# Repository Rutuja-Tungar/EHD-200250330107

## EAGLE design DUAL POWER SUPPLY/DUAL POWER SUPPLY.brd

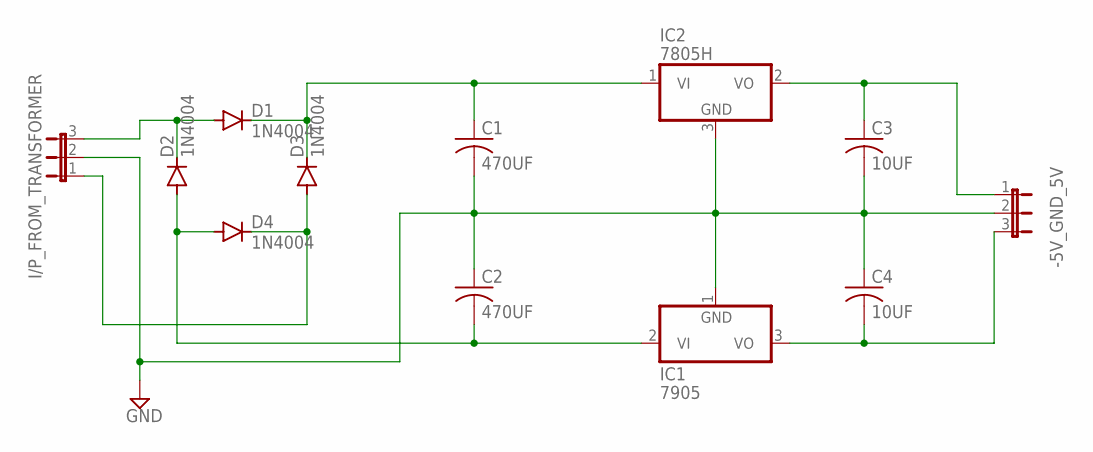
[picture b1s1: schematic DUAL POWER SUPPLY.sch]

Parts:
-5V_GND_5V: JP2W
C1, C2: 470UF; C025-024X044
C3, C4: 10UF; C025-024X044
D1, D2, D3, D4: 1N4004; DO41-10
I/P_FROM_TRANSFORMER: JP2W
IC1: 7905; TO39
IC2: 7805H; TO39

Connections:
GND: -5V_GND_5V.2, C1.2, C2.1, C3.2, C4.1, I/P_FROM_TRANSFORMER.2, IC1.1 (GND), IC2.3 (GND)
unnamed: D1.A, D2.C, I/P_FROM_TRANSFORMER.3
unnamed: C2.2, D2.A, D4.A, IC1.2 (VI)
unnamed: D3.A, D4.C, I/P_FROM_TRANSFORMER.1
unnamed: C1.1, D1.C, D3.C, IC2.1 (VI)
unnamed: -5V_GND_5V.1, C3.1, IC2.2 (VO)
unnamed: -5V_GND_5V.3, C4.2, IC1.3 (VO)

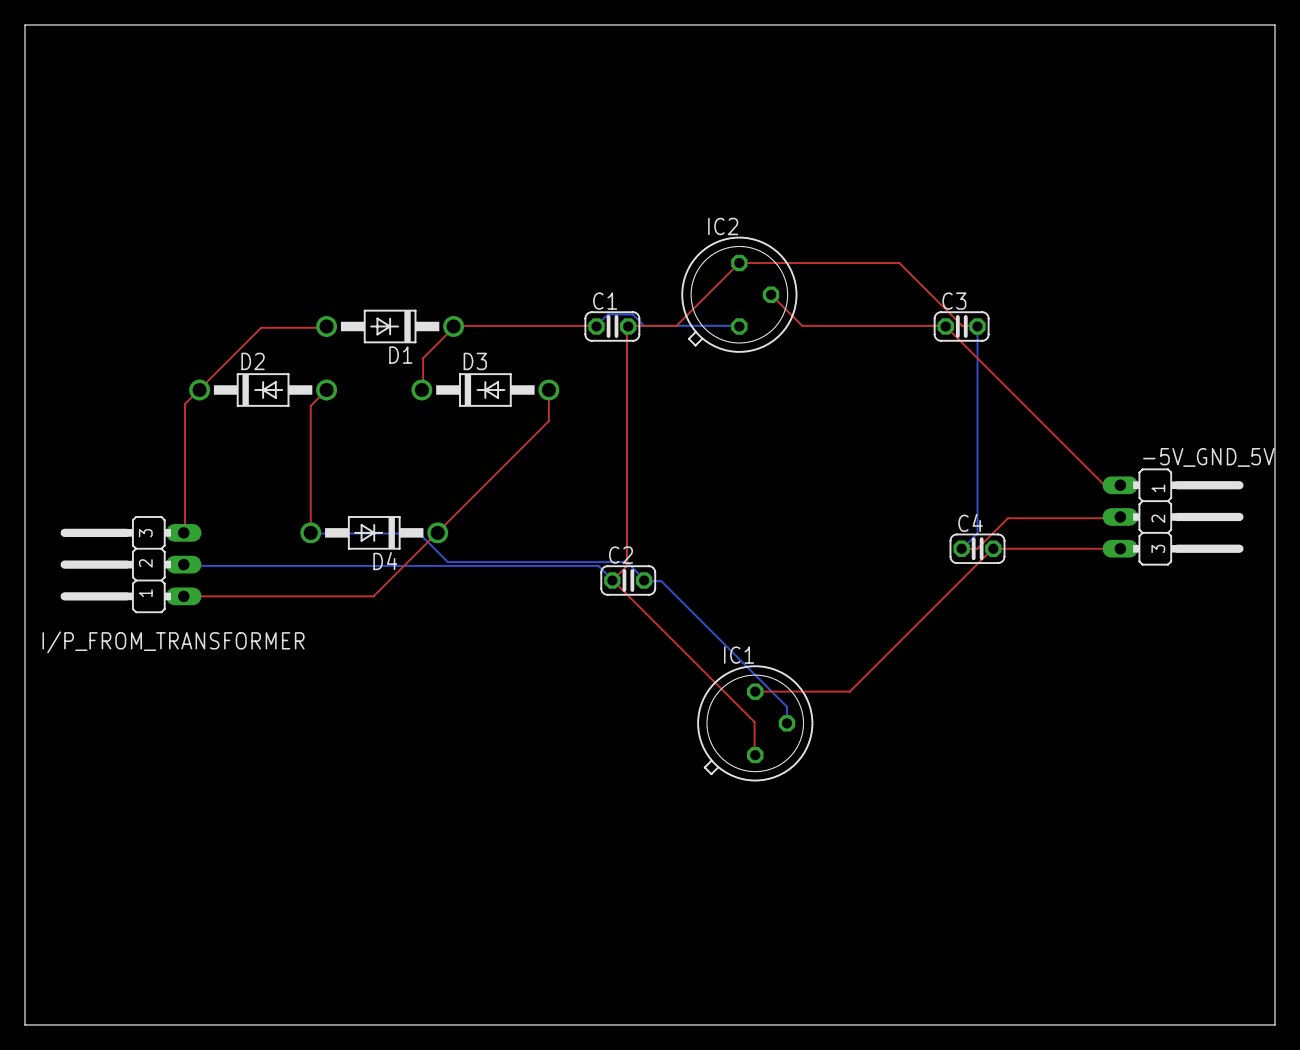
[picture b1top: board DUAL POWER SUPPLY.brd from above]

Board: 2 copper layers, 100.0 x 80.0 mm, 12 parts (0 on the bottom side), 7 nets.

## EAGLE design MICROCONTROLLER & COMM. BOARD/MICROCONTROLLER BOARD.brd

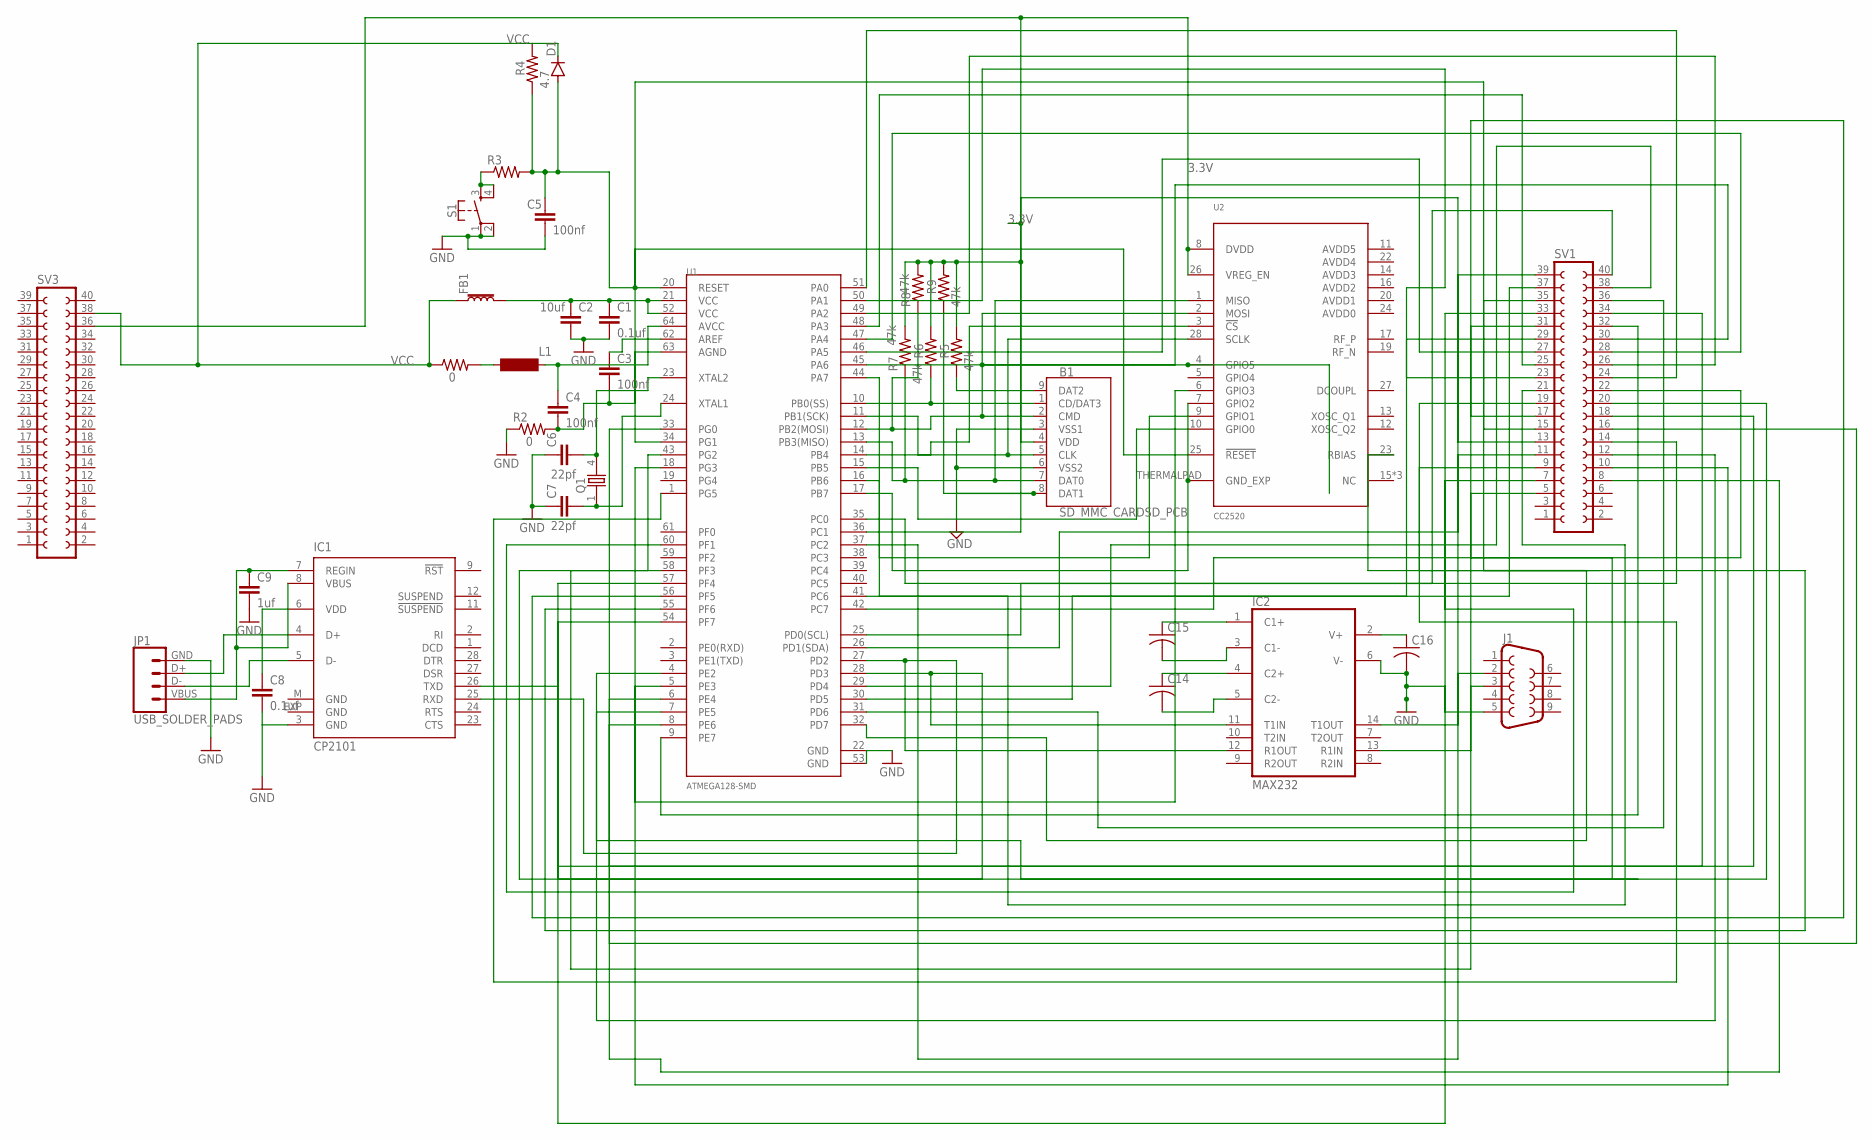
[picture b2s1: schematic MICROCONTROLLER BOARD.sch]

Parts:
B1: SD_MMC_CARDSD_PCB; SD-MMC-CARD
C1, C8: 0.1uf; C025-024X044
C2: 10uf; C025-024X044
C3, C4, C5: 100nf; C025-024X044
C6, C7: 22pf; C025-024X044
C9: 1uf; C025-024X044
C14, C15, C16: C-US025-024X044; C025-024X044
D1: 1N4004; DO41-10
FB1: FERRITE_BEAD-120_OHM-0402T; 0402-TIGHT
IC1: CP2101; MLP28
IC2: MAX232; DIL16
J1: DB9FEMALE; DB9
JP1: USB_SOLDER_PADS; USB-SOLDER-PADS
L1: BS11
Q1: 86SMX
R1, R2: 0; 0204V
R3: R-US_0204/2V; 0204V
R4: 4.7; 0204V
R5, R6, R7, R8, R9: 47k; 0204V
S1: MOMENTARY-SWITCH-SPST-2-SMD-4.6X2.8MM; TACTILE_SWITCH_SMD_4.6X2.8MM
SV1, SV3: FE20-2
U1: ATMEGA128-SMD; TQFP64_14X14MM
U2: CC2520; S-PVQFN-N28

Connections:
3.3V: B1.4 (VDD), R5.2, R6.2, R7.2, R8.2, R9.2, SV3.36, U2.8 (DVDD), U2.26 (VREG_EN)
GND: B1.3 (VSS1), B1.6 (VSS2), C1.2, C2.2, C5.2, C6.1, C7.1, C8.2, C9.2, C16.2, IC1.3 (GND), IC1.EXP (GND), IC1.M (GND), IC2.6 (V-), IC2.15 (GND), J1.5, JP1.GND (4), R2.1, S1.1, S1.2, U1.22 (GND), U1.53 (GND)
unnamed: C1.1, C2.1, FB1.2, U1.21 (VCC), U1.52 (VCC)
unnamed: L1.1, R1.2
unnamed: C4.1, L1.2, U1.64 (AVCC)
unnamed: C3.1, U1.62 (AREF)
unnamed: C3.2, C4.2, R2.2, U1.63 (AGND)
unnamed: SV1.18, U1.54 (PF7)
unnamed: R3.1, S1.3, S1.4
unnamed: C5.1, D1.A, R3.2, R4.1, U1.20 (RESET), U2.25 (!RESET)
unnamed: B1.8 (DAT1), R9.1
unnamed: SV1.40, U1.25 (PD0(SCL))
unnamed: C7.2, Q1.1, U1.24 (XTAL1)
unnamed: B1.7 (DAT0), R7.1, U1.13 (PB3(MISO)), U2.1 (MISO)
unnamed: B1.5 (CLK), U1.11 (PB1(SCK)), U2.28 (SCLK)
unnamed: B1.2 (CMD), R8.1, U1.12 (PB2(MOSI)), U2.2 (MOSI), U2.4 (GPIO5)
unnamed: U1.16 (PB6), U2.9 (GPIO1)
unnamed: B1.9 (DAT2), R5.1
unnamed: SV1.39, U1.26 (PD1(SDA))
unnamed: B1.1 (CD/DAT3), R6.1, U1.10 (PB0(SS))
unnamed: U1.14 (PB4), U2.3 (!CS)
unnamed: U1.15 (PB5), U2.10 (GPIO0)
unnamed: U1.17 (PB7), U2.7 (GPIO2), U2.THERMALPAD (GND_EXP)
unnamed: U1.18 (PG3), U2.6 (GPIO3)
unnamed: SV1.38, U1.29 (PD4)
unnamed: SV1.37, U1.30 (PD5)
unnamed: IC1.26 (TXD), IC2.11 (T1IN), U1.28 (PD3)
unnamed: IC1.25 (RXD), IC2.12 (R1OUT), U1.27 (PD2)
unnamed: C9.1, IC1.7 (REGIN), IC1.8 (VBUS), JP1.VBUS (1)
unnamed: C15.1, IC2.1 (C1+)
unnamed: IC1.4 (D+), JP1.D+ (3)
unnamed: IC1.5 (D-), JP1.D- (2)
unnamed: C15.2, IC2.3 (C1-)
unnamed: C8.1, IC1.6 (VDD)
unnamed: C14.1, IC2.4 (C2+)
unnamed: C14.2, IC2.5 (C2-)
unnamed: C16.1, IC2.2 (V+)
unnamed: SV1.36, U1.31 (PD6)
unnamed: IC2.14 (T1OUT), J1.2
unnamed: IC2.13 (R1IN), J1.3
unnamed: SV1.35, U1.32 (PD7)
unnamed: SV1.33, U1.60 (PF1)
unnamed: SV1.34, U1.8 (PE6)
unnamed: SV1.31, U1.7 (PE5)
unnamed: SV1.32, U1.9 (PE7)
unnamed: SV1.29, U1.44 (PA7)
unnamed: SV1.30, U1.45 (PA6)
unnamed: SV1.27, U1.46 (PA5)
unnamed: SV1.28, U1.47 (PA4)
unnamed: SV1.25, U1.48 (PA3)
unnamed: SV1.26, U1.49 (PA2)
unnamed: SV1.23, U1.50 (PA1)
unnamed: SV1.24, U1.51 (PA0)
unnamed: SV1.21, U1.41 (PC6)
unnamed: SV1.22, U1.42 (PC7)
unnamed: SV1.20, U1.43 (PG2)
unnamed: C6.2, Q1.4 (2), U1.23 (XTAL2)
unnamed: SV1.16, U1.33 (PG0)
unnamed: SV1.17, U1.56 (PF5)
unnamed: SV1.19, U1.55 (PF6)
unnamed: SV1.15, U1.34 (PG1)
unnamed: SV1.14, U1.35 (PC0)
unnamed: SV1.13, U1.36 (PC1)
unnamed: SV1.9, U1.1 (PG5)
unnamed: SV1.12, U1.4 (PE2)
unnamed: SV1.10, U1.5 (PE3)
unnamed: SV1.11, U1.37 (PC2)
unnamed: SV1.7, U1.57 (PF4)
unnamed: SV1.5, U1.58 (PF3)
unnamed: SV1.8, U1.6 (PE4)
VCC: D1.C, FB1.1, IC2.16 (VCC), R1.1, R4.2, SV3.38

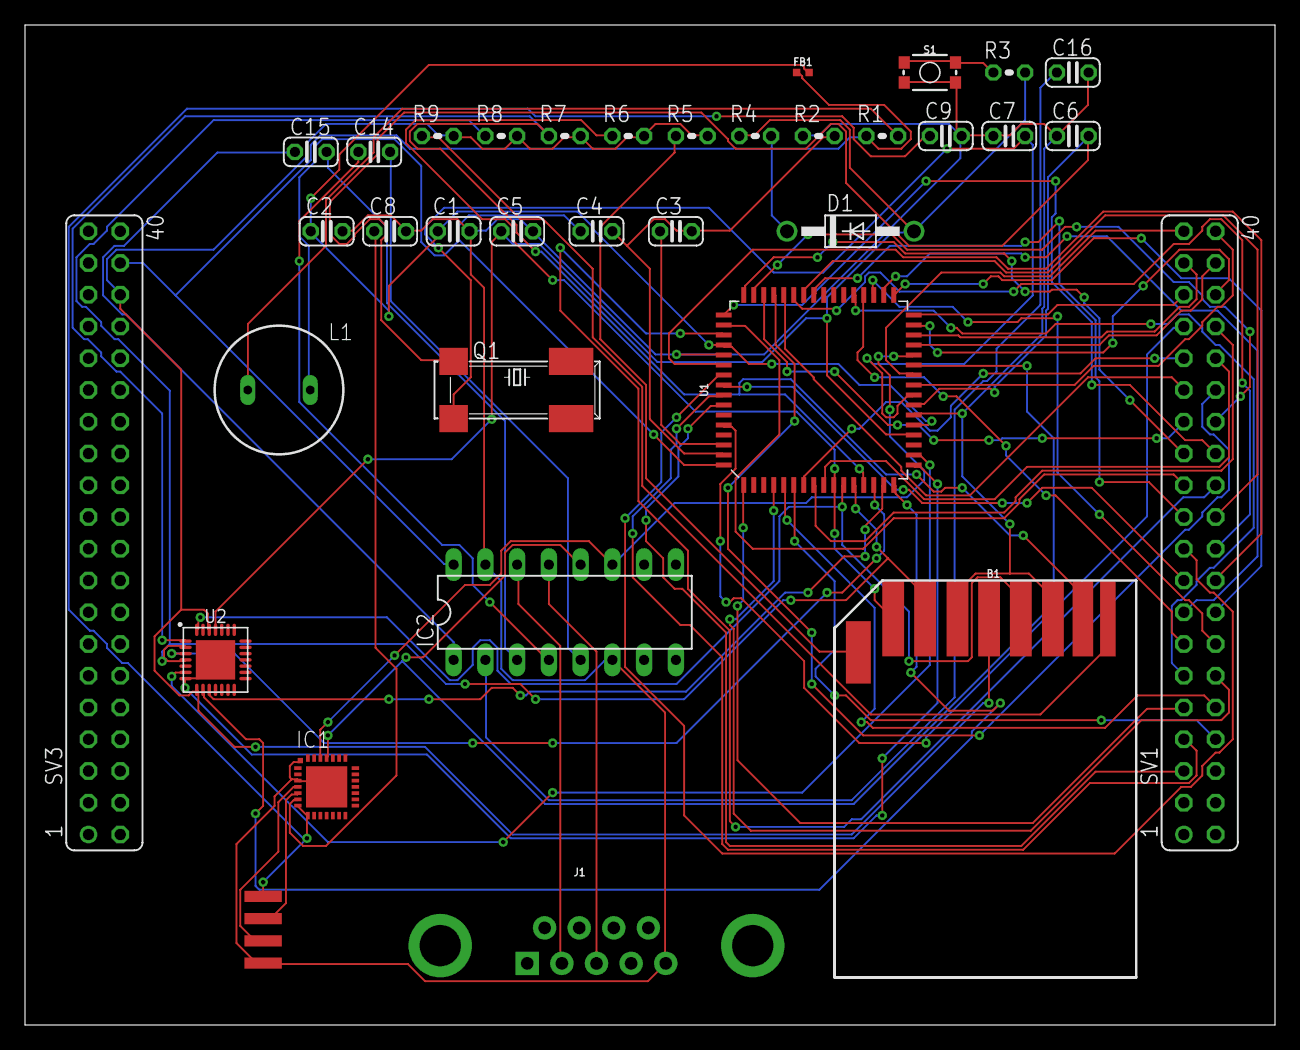
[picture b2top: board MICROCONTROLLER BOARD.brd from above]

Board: 2 copper layers, 100.0 x 80.0 mm, 35 parts (0 on the bottom side), 71 nets.

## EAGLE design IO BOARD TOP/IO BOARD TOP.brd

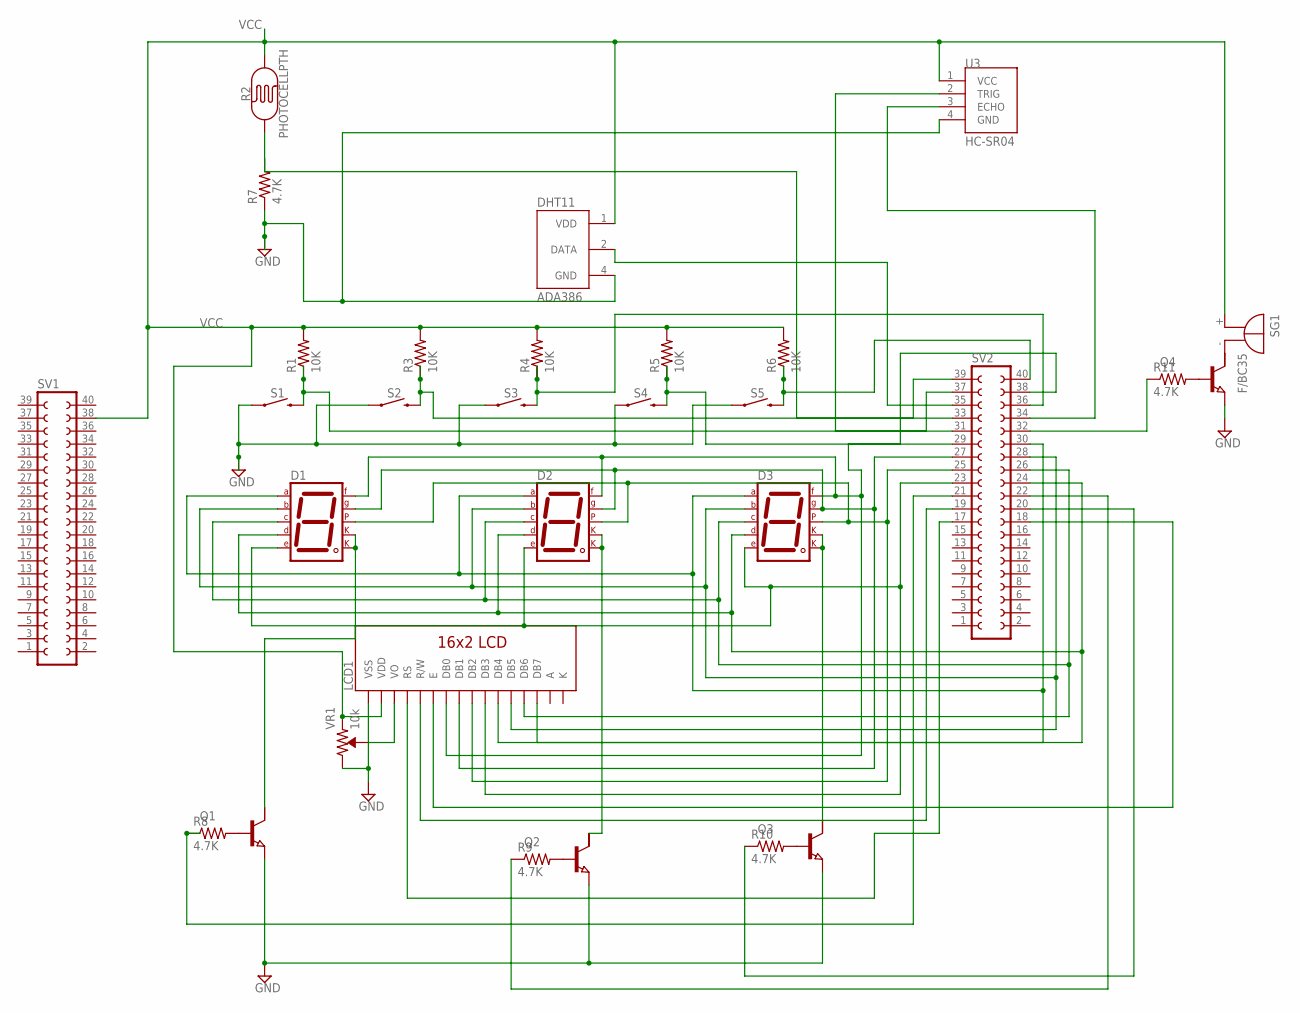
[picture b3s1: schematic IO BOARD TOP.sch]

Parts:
D1, D2, D3: 7SEG-CK; 7SEG-13
DHT11: ADA386; XDCR_ADA386
LCD1: LCD-16X2SILK; LCD-16X2
Q1, Q2, Q3, Q4: NPN-TRANSISTIOR-2COLSOT89; SOT89
R1, R3, R4, R5, R6: 10K; 0204V
R2: PHOTOCELLPTH; PHOTOCELL
R7, R8, R9, R10, R11: 4.7K; 0204V
S1, S2, S3, S4: MOMENTARY-SWITCH-SPST-SMD-4.6X2.8MM; TACTILE_SWITCH_SMD_4.6X2.8MM
S5: MOMENTARY-SWITCH-SPST-SMD-5.2-REDUNDANT; TACTILE_SWITCH_SMD_5.2MM
SG1: F/BC35
SV1, SV2: FE20-2
U3: HC-SR04; XCVR_HC-SR04
VR1: 10k; TRIMPOT-SMD-TC33X

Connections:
A: LCD1.15 (A)
GND: DHT11.4 (GND), LCD1.1 (VSS), Q1.3 (E), Q2.3 (E), Q3.3 (E), Q4.3 (E), R7.1, S1.1, S1.2 (1), S2.1, S2.2 (1), S3.1, S3.2 (1), S4.1, S4.2 (1), S5.1, S5.2 (1), U3.4 (GND), VR1.1 (CW)
K: LCD1.16 (K)
unnamed: R1.1, S1.3 (2), S1.4 (2), SV2.37
unnamed: R3.1, S2.3 (2), S2.4 (2), SV2.39
unnamed: R4.1, S3.3 (2), S3.4 (2), SV2.36
unnamed: R5.1, S4.3 (2), S4.4 (2), SV2.38
unnamed: R6.1, S5.3 (2), S5.4 (2), SV2.40
unnamed: DHT11.2 (DATA), SV2.35
unnamed: LCD1.3 (VO), VR1.2 (WIPER)
unnamed: SV2.31, U3.2 (TRIG)
unnamed: SV2.34, U3.3 (ECHO)
unnamed: D1.9 (F), D2.9 (F), D3.9 (F), LCD1.7 (DB0), SV2.29
unnamed: Q4.1 (B), R11.2
unnamed: D1.6 (B), D2.6 (B), D3.6 (B), LCD1.12 (DB5), SV2.28
unnamed: R2.1, R7.2, SV2.33
unnamed: D1.4 (C), D2.4 (C), D3.4 (C), LCD1.13 (DB6), SV2.26
unnamed: D1.10 (G), D2.10 (G), D3.10 (G), LCD1.8 (DB1), SV2.27
unnamed: D1.3 (CK1), D1.8 (CK2), Q1.2 (C)
unnamed: D1.1 (E), D2.1 (E), D3.1 (E), LCD1.10 (DB3), SV2.23
unnamed: D1.7 (A), D2.7 (A), D3.7 (A), LCD1.11 (DB4), SV2.30
unnamed: D2.3 (CK1), D2.8 (CK2), Q2.2 (C)
unnamed: D3.3 (CK1), D3.8 (CK2), Q3.2 (C)
unnamed: D1.2 (D), D2.2 (D), D3.2 (D), LCD1.14 (DB7), SV2.24
unnamed: D1.5 (DP), D2.5 (DP), D3.5 (DP), LCD1.9 (DB2), SV2.25
unnamed: Q1.1 (B), R8.2
unnamed: Q2.1 (B), R9.2
unnamed: Q3.1 (B), R10.2
unnamed: R9.1, SV2.22
unnamed: R10.1, SV2.20
unnamed: Q4.2 (C), SG1.-
unnamed: R11.1, SV2.32
unnamed: LCD1.6 (E), SV2.18
unnamed: LCD1.5 (R/W), SV2.19
unnamed: LCD1.4 (RS), SV2.17
unnamed: R8.1, SV2.21
VCC: DHT11.1 (VDD), LCD1.2 (VDD), R1.2, R2.2, R3.2, R4.2, R5.2, R6.2, SG1.+, SV1.38, U3.1 (VCC), VR1.3 (CCW)

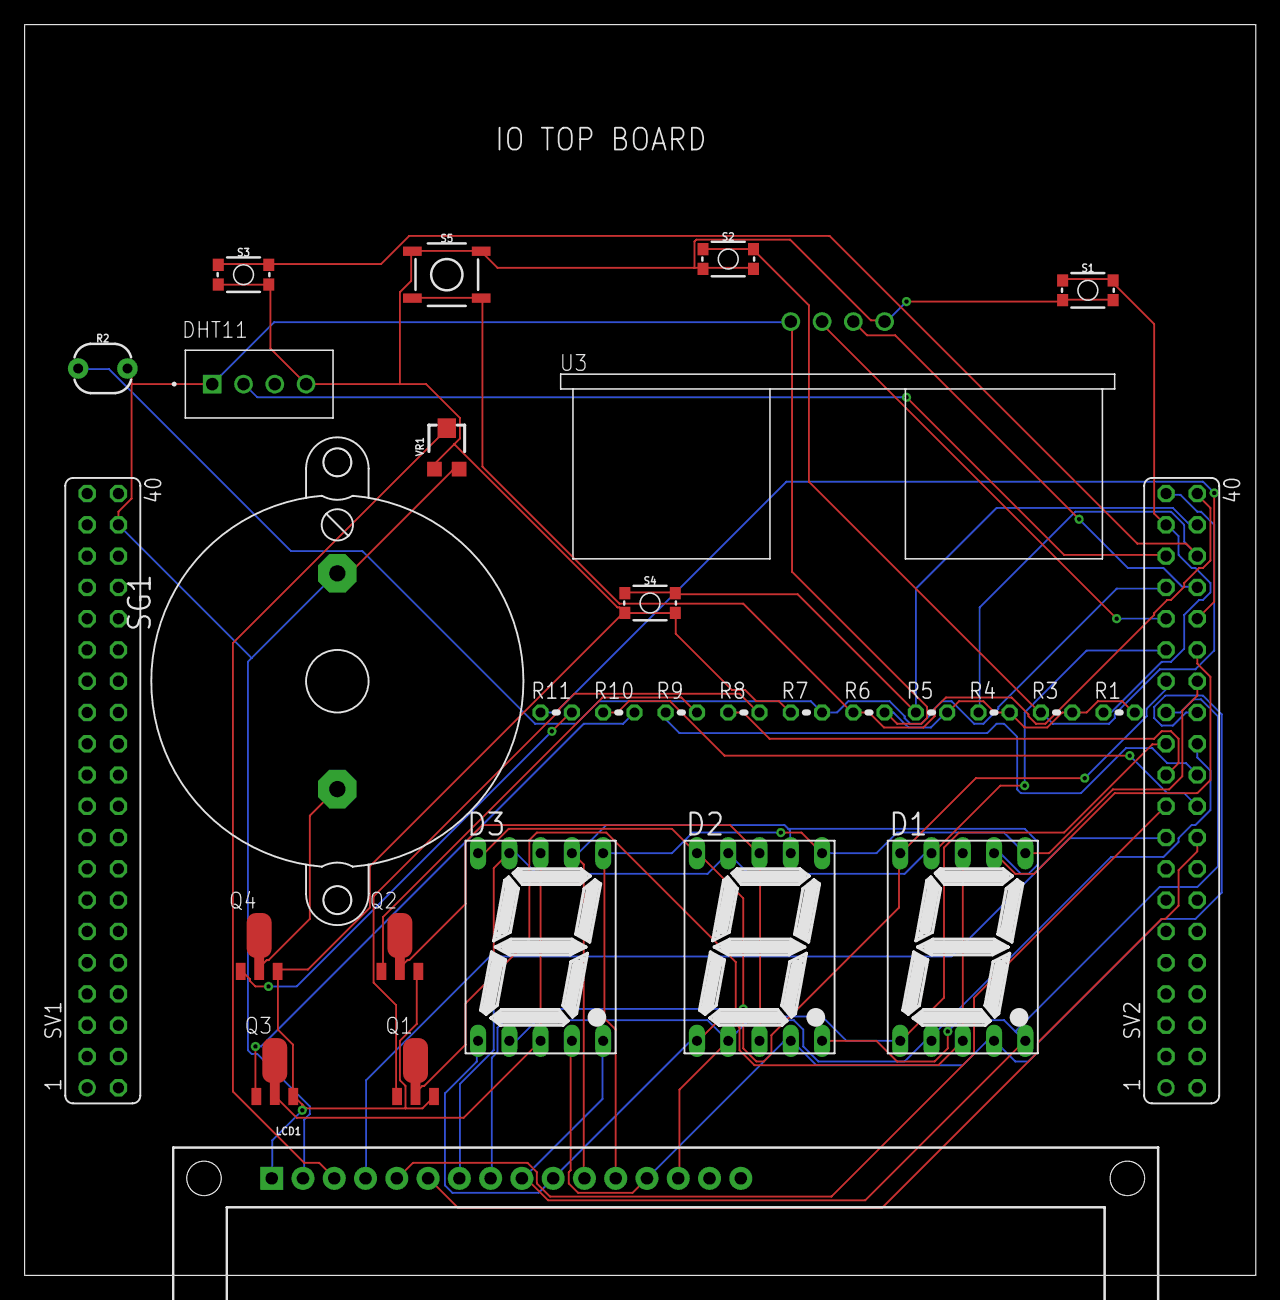
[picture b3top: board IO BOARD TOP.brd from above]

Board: 2 copper layers, 100.0 x 101.6 mm, 30 parts (0 on the bottom side), 35 nets.

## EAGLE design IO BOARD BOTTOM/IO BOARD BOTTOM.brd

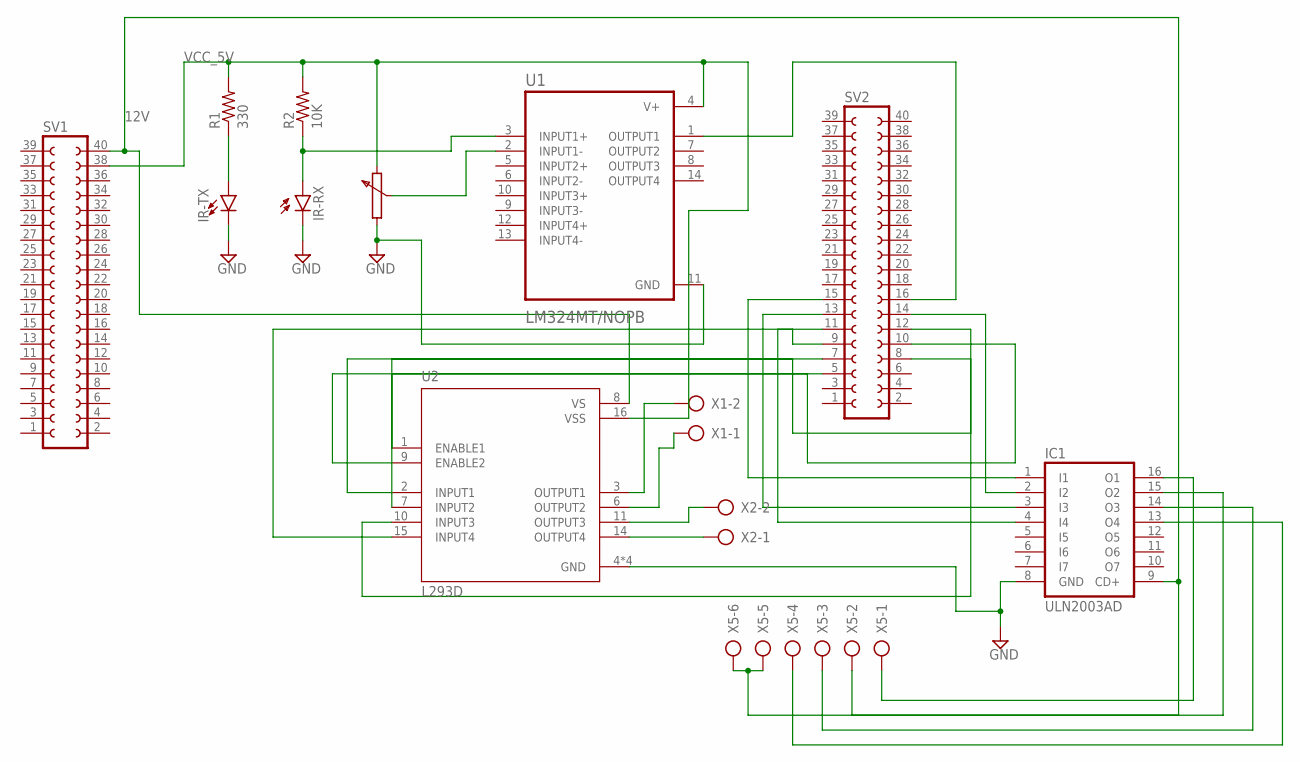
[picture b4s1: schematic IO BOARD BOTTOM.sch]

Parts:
IC1: ULN2003AD; SO16
IR-RX: SFH205
IR-TX: LED-IRTSAL6100; LED_5MM
R1: 330; 0204V
R2: 10K; 0204V
SV1, SV2: FE20-2
U1: LM324MT/NOPB; SOP65P640X120-14N
U2: L293D; DIP880W50P254L2000H510Q16
X1, X2: AK500/2
X5: AK500/6

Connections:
12V: IC1.9 (CD+), SV1.40, U2.8 (VS), X5.5, X5.6
GND: IC1.8 (GND), IR-RX.K (C), IR-TX.K (C), U1.11 (GND), U2.4 (GND), U2.5 (GND), U2.12 (GND), U2.13 (GND)
unnamed: IR-TX.A, R1.1
unnamed: IR-RX.A, R2.1, U1.3 (INPUT1+)
unnamed: SV2.16, U1.1 (OUTPUT1)
unnamed: SV2.8, U2.1 (ENABLE1)
unnamed: SV2.10, U2.9 (ENABLE2)
unnamed: SV2.7, U2.2 (INPUT1)
unnamed: SV2.5, U2.7 (INPUT2)
unnamed: SV2.12, U2.10 (INPUT3)
unnamed: SV2.9, U2.15 (INPUT4)
unnamed: U2.3 (OUTPUT1), X1.2
unnamed: U2.6 (OUTPUT2), X1.1
unnamed: U2.11 (OUTPUT3), X2.2
unnamed: U2.14 (OUTPUT4), X2.1
unnamed: IC1.1 (I1), SV2.15
unnamed: IC1.2 (I2), SV2.14
unnamed: IC1.3 (I3), SV2.13
unnamed: IC1.4 (I4), SV2.11
unnamed: IC1.16 (O1), X5.1
unnamed: IC1.15 (O2), X5.2
unnamed: IC1.14 (O3), X5.3
unnamed: IC1.13 (O4), X5.4
VCC_5V: R1.2, R2.2, SV1.38, U1.4 (V+), U2.16 (VSS)

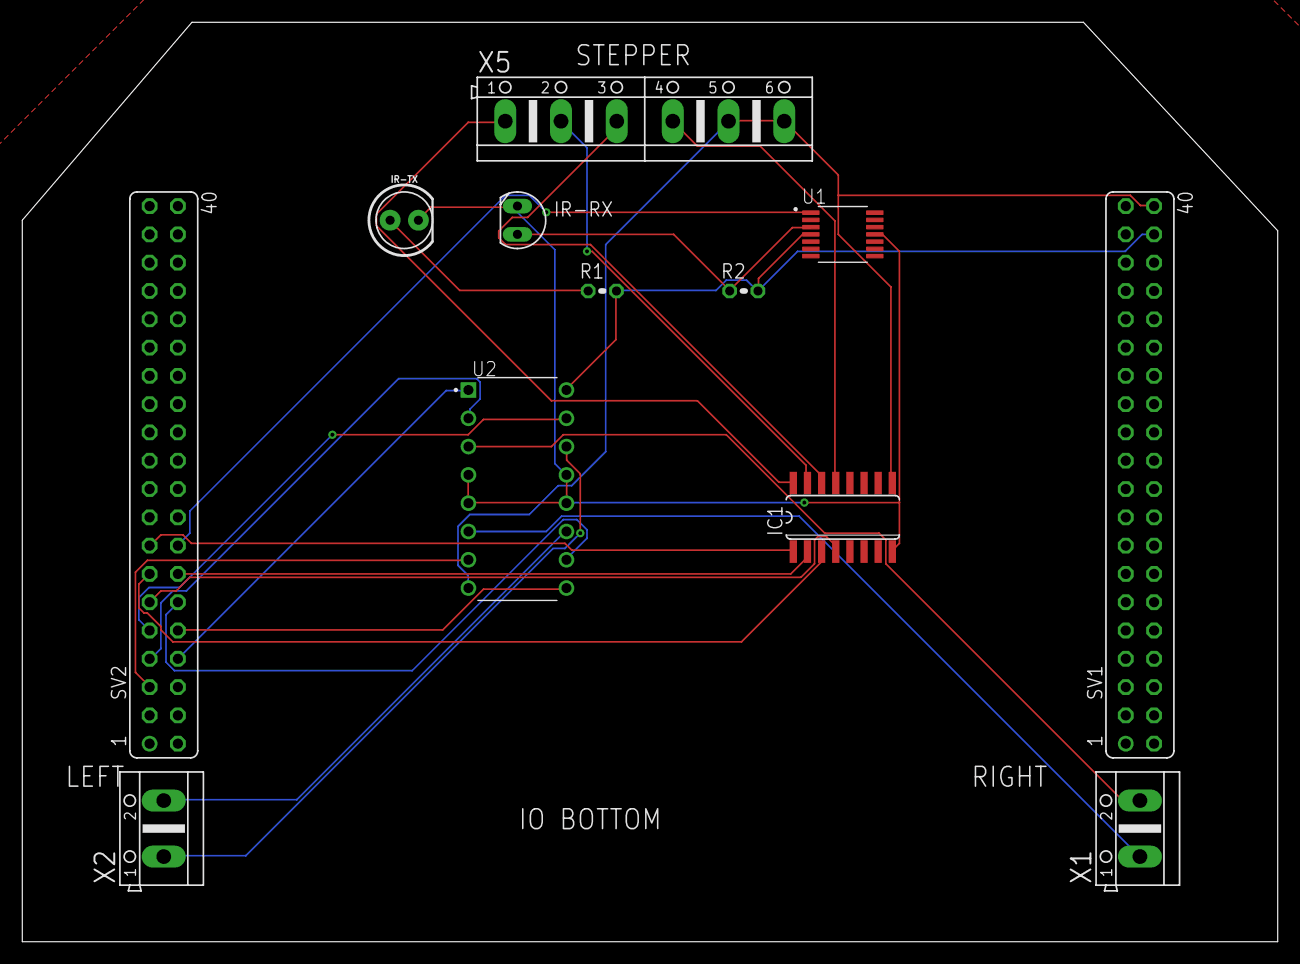
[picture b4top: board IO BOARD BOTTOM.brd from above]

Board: 2 copper layers, 112.7 x 82.5 mm, 12 parts (0 on the bottom side), 24 nets.

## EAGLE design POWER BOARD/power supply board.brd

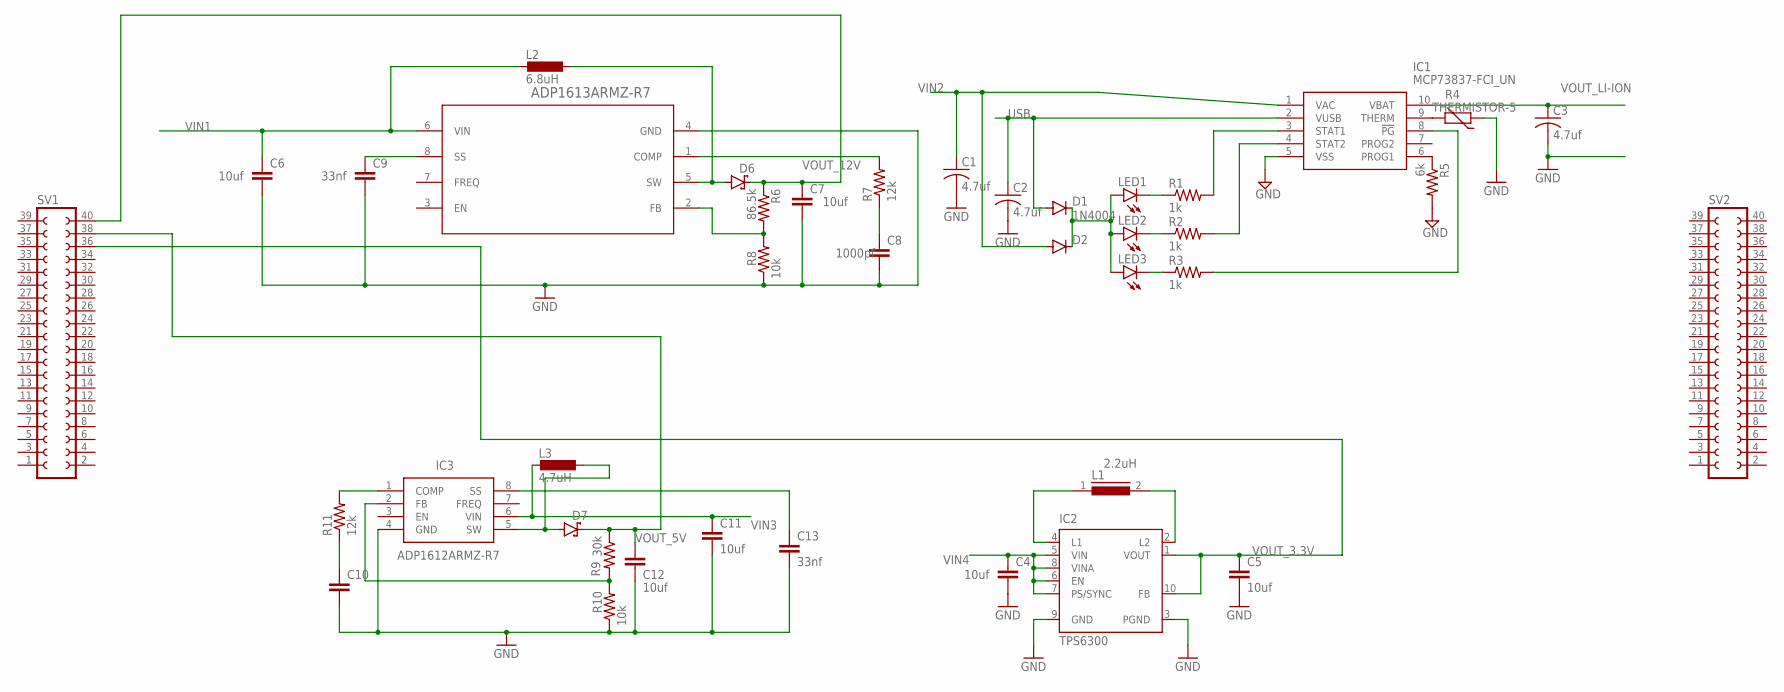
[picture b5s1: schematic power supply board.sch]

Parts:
C1, C2, C3: 4.7uf; C025-024X044
C4, C5, C6, C7, C11, C12: 10uf; C2.5-3
C8: 1000pf; C2.5-3
C9, C13: 33nf; C2.5-3
C10: 1200pf; C2.5-3
D1, D2: 1N4004; DO41-10
D6, D7: 3A,40V; SMC
IC1: MCP73837-FCI_UN; SOP50P490X110-10N
IC2: TPS6300; DRC-S-PVSON-N10
IC3: ADP1612ARMZ-R7; SOP65P490X110-8N
L1: 2.2uH; SLF7045
L2: 6.8uH; DO3316P
L3: 4.7uH; DO3316P
LED1, LED2, LED3: LAP4-BOTTOM; P47F-BOTTOM
R1, R2, R3: 1k; 0204V
R4: THERMISTOR-5; R-5
R5: 6k; 0204V
R6: 86.5k; M0805
R7, R11: 12k; M0805
R8, R10: 10k; M0805
R9: 30k; M0805
SV1, SV2: FE20-2
U1: ADP1613ARMZ-R7; RM_8_ADI

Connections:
GND: C1.2, C2.2, C3.2, C4.2, C5.2, C6.2, C7.2, C8.2, C9.2, C10.2, C11.2, C12.2, C13.2, IC1.5 (VSS), IC2.3 (PGND), IC2.9 (GND), IC3.4 (GND), R4.1, R5.2, R8.1, R10.1, U1.4 (GND)
unnamed: LED1.C, R1.1
unnamed: LED2.C, R2.1
unnamed: D1.C, D2.C, LED1.A, LED2.A, LED3.A
unnamed: IC1.3 (STAT1), R1.2
unnamed: LED3.C, R3.1
unnamed: IC1.4 (STAT2), R2.2
unnamed: IC1.8 (!PG), R3.2
unnamed: IC1.6 (PROG1), R5.1
unnamed: IC1.9 (THERM), R4.2
unnamed: IC2.4 (L1), L1.1
unnamed: C13.1, IC3.8 (SS)
unnamed: IC2.2 (L2), L1.2
unnamed: D6.A, L2.2, U1.5 (SW)
unnamed: C10.1, R11.1
unnamed: C9.1, U1.8 (SS)
unnamed: R6.2, R8.2, U1.2 (FB)
unnamed: IC3.1 (COMP), R11.2
unnamed: R7.2, U1.1 (COMP)
unnamed: C8.1, R7.1
unnamed: IC3.2 (FB), R9.2, R10.2
USB: C2.1, D1.A, IC1.2 (VUSB)
VIN1: C6.1, L2.1, U1.6 (VIN)
VIN2: C1.1, D2.A, IC1.1 (VAC)
VIN3: C11.1, IC3.6 (VIN), L3.1
VIN4: C4.1, IC2.5 (VIN), IC2.6 (EN), IC2.7 (PS/SYNC), IC2.8 (VINA)
VOUT1: D7.A, IC3.5 (SW), L3.2
VOUT_3.3V: C5.1, IC2.1 (VOUT), IC2.10 (FB), SV1.36
VOUT_5V: C12.1, D7.C, R9.1, SV1.38
VOUT_12V: C7.1, D6.C, R6.1, SV1.40
VOUT_LI-ION: C3.1, IC1.10 (VBAT)

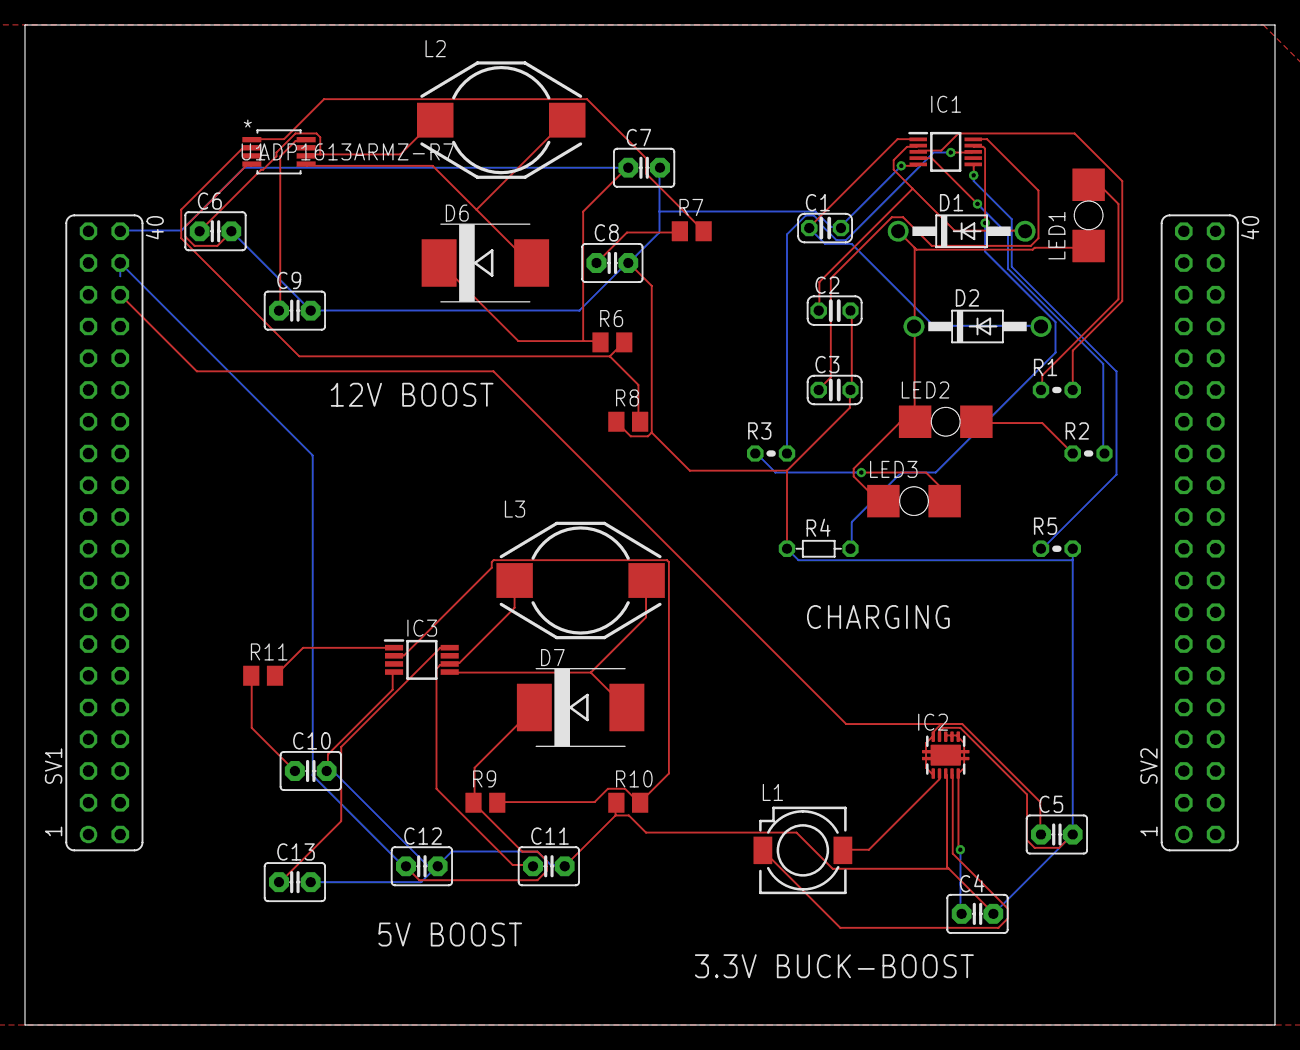
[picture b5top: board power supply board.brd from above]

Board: 2 copper layers, 100.0 x 80.0 mm, 40 parts (0 on the bottom side), 31 nets.

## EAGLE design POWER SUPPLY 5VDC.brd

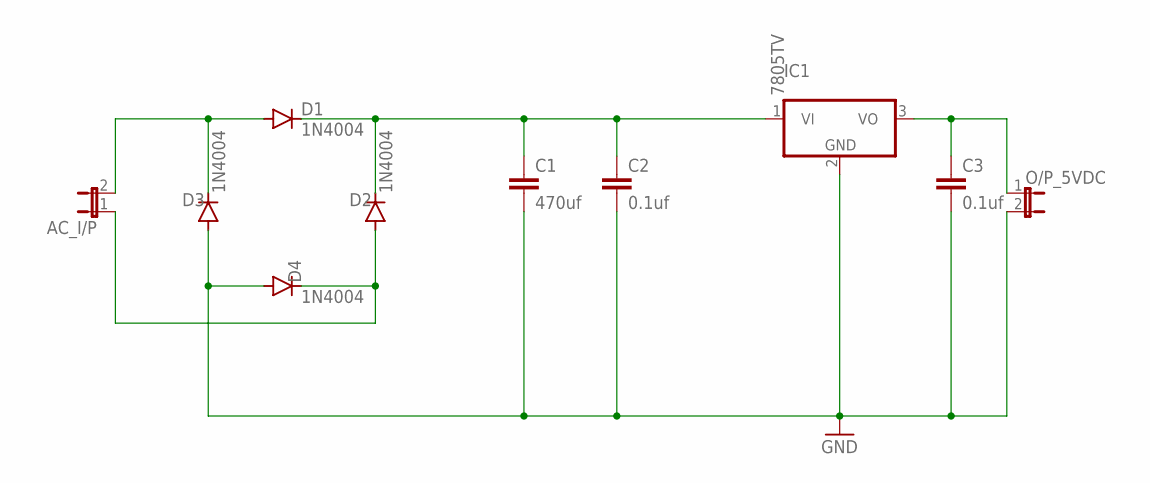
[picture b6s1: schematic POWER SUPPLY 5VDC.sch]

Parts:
AC_I/P: 12VAC; JP1
C1: 470uf; C025-024X044
C2, C3: 0.1uf; C025-024X044
D1, D2, D3, D4: 1N4004; DO41-10
IC1: 7805TV; TO220V
O/P_5VDC: 5VDC; JP1

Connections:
GND: C1.2, C2.2, C3.2, D3.A, D4.A, IC1.2 (GND), O/P_5VDC.2
unnamed: AC_I/P.2, D1.A, D3.C
unnamed: C1.1, C2.1, D1.C, D2.C, IC1.1 (VI)
unnamed: C3.1, IC1.3 (VO), O/P_5VDC.1
unnamed: AC_I/P.1, D2.A, D4.C

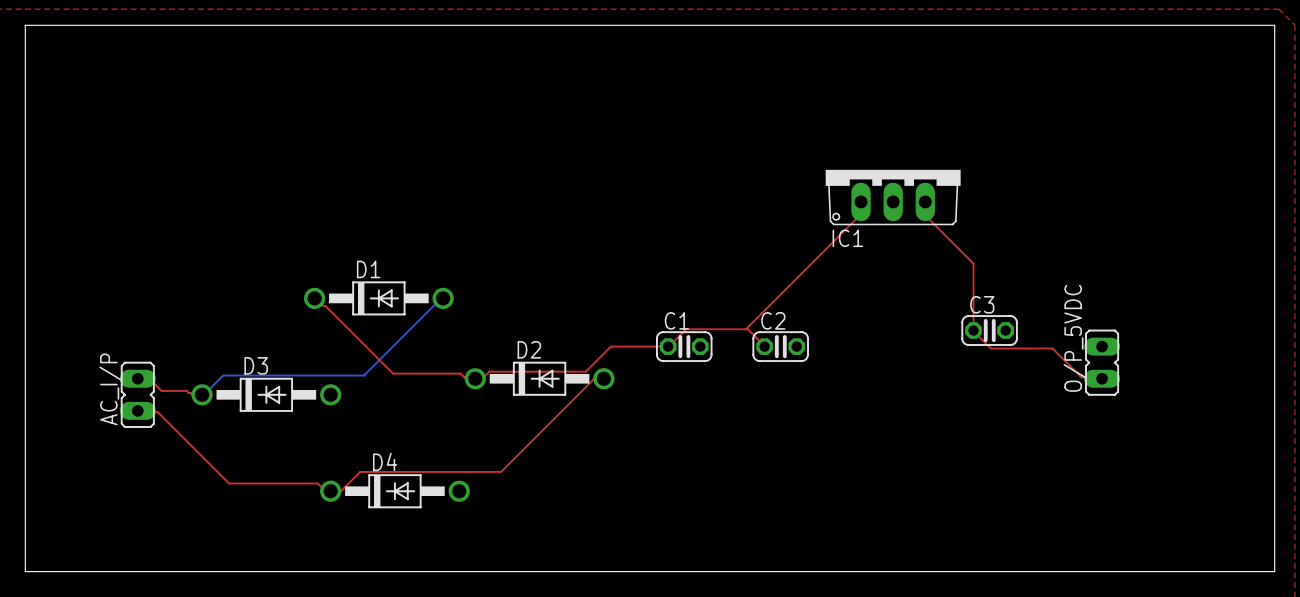
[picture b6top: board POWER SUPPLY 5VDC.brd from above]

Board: 2 copper layers, 98.7 x 43.2 mm, 10 parts (0 on the bottom side), 5 nets.

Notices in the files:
parts and their libraries:
SparkFun-LED: Licensing: Creative Commons ShareAlike 4.0 International - https://creativecommons.org/licenses/by-sa/4.0
